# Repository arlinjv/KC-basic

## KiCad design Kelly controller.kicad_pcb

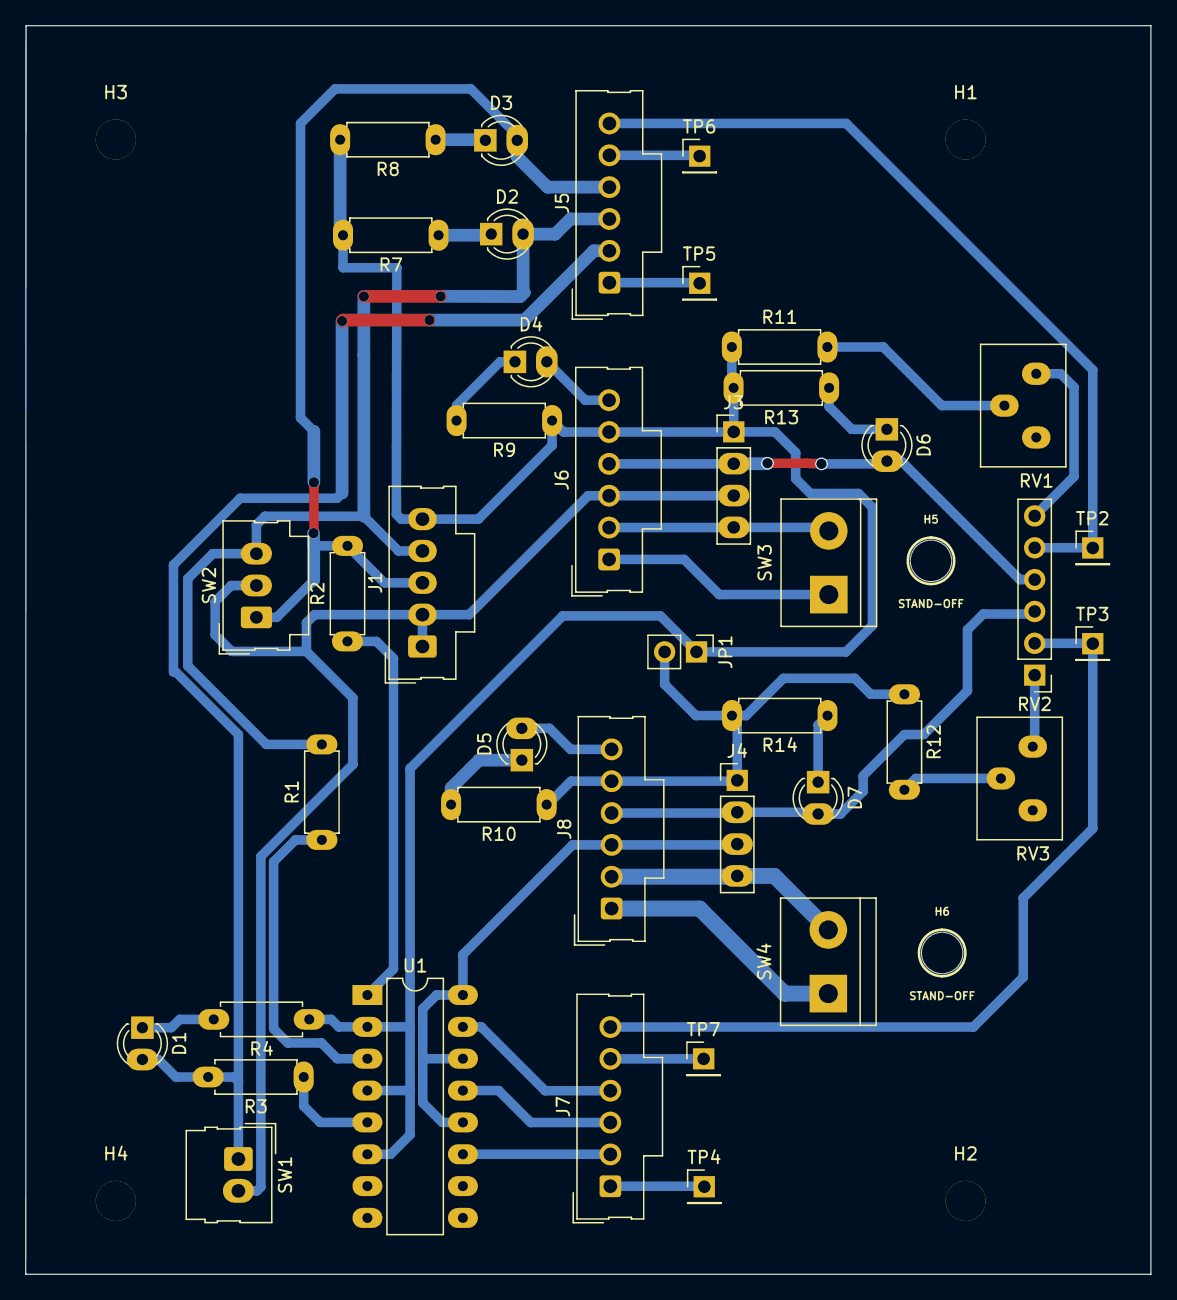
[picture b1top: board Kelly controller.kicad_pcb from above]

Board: 2 copper layers, 89.8 x 99.6 mm, 47 parts (0 on the bottom side), 38 nets.

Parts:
D1, D4, D5: yellow; LED_D3.0mm_wide_pads
D2, D3: green; LED_D3.0mm_wide_pads
D6, D7: RED; LED_D3.0mm_wide_pads
H1, H2, H3, H4: MountingHole; MountingHole_3.2mm_M3_through_hole
H5, H6: STAND-OFF
J1: FNR switch; Molex_SL_171971-0005_1x05_P2.54mm_Vertical
J3: A_5_12_48; PinHeader_1x04_P2.54mm_Vertical_wide_pads
J4: B_5_12_48; PinHeader_1x04_P2.54mm_Vertical_wide_pads
J5, J6, J7, J8: Conn_01x06_Female; Molex_SL_171971-0006_1x06_P2.54mm_Vertical
JP1: Jumper_2_Open; PinHeader_1x02_P2.54mm_Vertical
R1, R2, R3, R9, R10, R11, R12, R13, R14: 1k; R_Axial_DIN0207_L6.3mm_D2.5mm_P7.62mm_Horizontal_wide_pads
R4, R7, R8: 2.2k; R_Axial_DIN0207_L6.3mm_D2.5mm_P7.62mm_Horizontal_wide_pads
RV1, RV3: trim(1k); trimpot_breadboard_spacing
RV2: throttle(10k); PinHeader_1x06_P2.54mm_Vertical
SW1: Brake_SW; Molex_SL_171971-0002_1x02_P2.54mm_Vertical
SW2: FNR; Molex_SL_171971-0003_1x03_P2.54mm_Vertical_wide_pads
SW3, SW4: Power Switch; TerminalBlock_bornier-2_P5.08mm
TP2: T_A; PinHeader_1x01_P2.54mm_Vertical
TP3: T_B; PinHeader_1x01_P2.54mm_Vertical
TP4, TP5: ftsw; PinHeader_1x01_P2.54mm_Vertical
TP6, TP7: anbrk; PinHeader_1x01_P2.54mm_Vertical
U1: LTV-247; DIP-16_W7.62mm_LongPads

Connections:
+5VA: D6.2, J3.2, J6.4, RV2.4
+5VB: D7.2, J4.2, J8.4, RV2.3
+12VA: J1.1, J1.2, J3.3, J6.3, SW1.2, SW2.2
+12VB: J4.3, J8.3, U1.12, U1.14, U1.16
+48VA: J3.4, J6.2, SW3.2
+48VB: J4.4, J8.2, SW4.2
/Brake-A: D1.2, J5.2, R3.2, SW1.1
/Brake-B: J7.2, U1.11
/Brake_AN-A: J5.5, TP6.1
/Brake_AN-B: J7.5, TP7.1
/FWD-A: D3.2, J1.3, J5.4, R2.2, SW2.1
/FWD-B: J7.4, U1.15
/Foot_SW-A: J5.1, TP5.1
/Foot_SW-B: J7.1, TP4.1
/Meter-A: D4.2, J6.6
/Meter-B: D5.2, J8.6
/PWR-A: J6.1, SW3.1
/PWR-B: J8.1, SW4.1
/REV-A: D2.2, J1.4, J5.3, R1.2, SW2.3
/REV-B: J7.3, U1.13
/Throttle-A: J5.6, RV2.5, TP2.1
/Throttle-B: J7.6, RV2.2, TP3.1
GNDA: J1.5, J3.1, J6.5, JP1.1, R4.1, R7.2, R8.2, R9.1, R11.1, R13.2, U1.2, U1.4, U1.6
GNDB: J4.1, J8.5, JP1.2, R10.1, R12.1, R14.2
unnamed: D1.1, R4.2
unnamed: D2.1, R7.1
unnamed: D3.1, R8.1
unnamed: D4.1, R9.2
unnamed: D5.1, R10.2
unnamed: D6.1, R13.1
unnamed: D7.1, R14.1
unnamed: R1.1, U1.3
unnamed: R2.1, U1.1
unnamed: R3.1, U1.5
unnamed: R11.2, RV1.2
unnamed: R12.2, RV3.2
unnamed: RV1.1, RV2.6
unnamed: RV2.1, RV3.1

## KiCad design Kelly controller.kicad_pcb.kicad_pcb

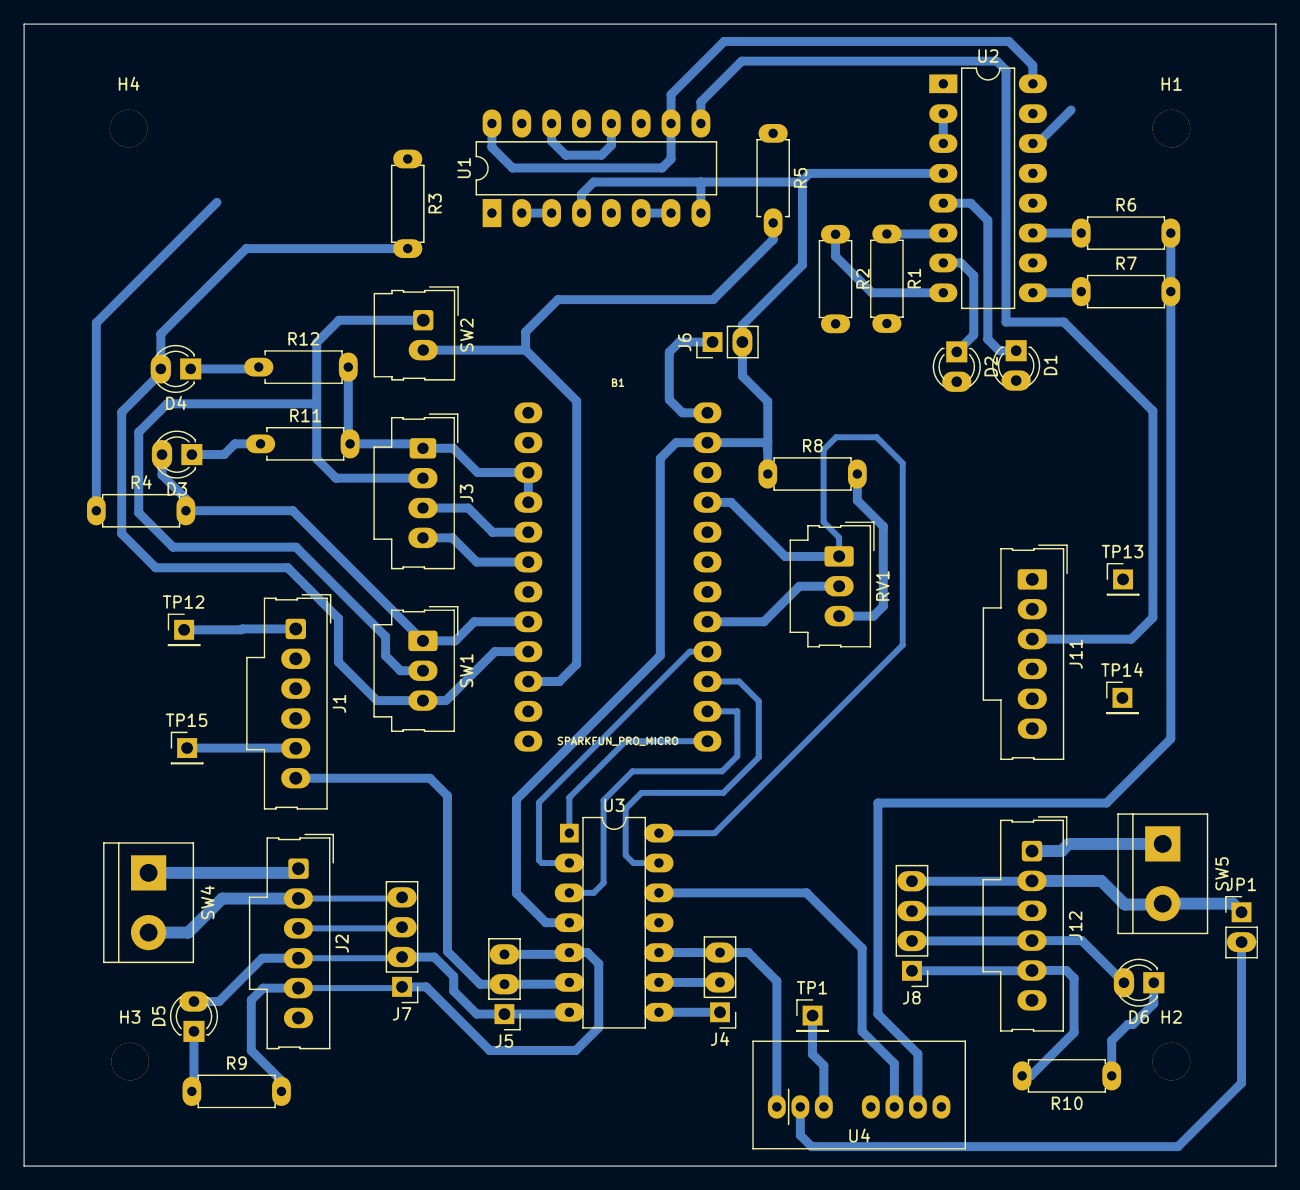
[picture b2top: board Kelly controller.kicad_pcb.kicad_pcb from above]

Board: 2 copper layers, 106.5 x 97.2 mm, 48 parts (0 on the bottom side), 56 nets.

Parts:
B1: SPARKFUN_PRO_MICRO
D1, D2: yellow; LED_D3.0mm_wide_pads
D3, D4: green; LED_D3.0mm_wide_pads
D5, D6: RED; LED_D3.0mm_wide_pads
H1, H2, H3, H4: MountingHole; MountingHole_3.2mm_M3_through_hole
J1, J2, J11, J12: Conn_01x06_Female; Molex_SL_171971-0006_1x06_P2.54mm_Vertical
J3: I2C throttle; Molex_SL_171971-0004_1x04_P2.54mm_Vertical_wide_pads
J4: throttle A; PinHeader_1x03_P2.54mm_Vertical_wide_pads
J5: throttle B; PinHeader_1x03_P2.54mm_Vertical_wide_pads
J6: Board power; PinHeader_1x02_P2.54mm_Vertical
J7: B_5_12_48; PinHeader_1x04_P2.54mm_Vertical_wide_pads
J8: A_5_12_48; PinHeader_1x04_P2.54mm_Vertical_wide_pads
JP1: Jumper; PinHeader_1x02_P2.54mm_Vertical
R1, R2, R8, R9, R10, R11, R12: 1k; R_Axial_DIN0207_L6.3mm_D2.5mm_P7.62mm_Horizontal_wide_pads
R3, R4, R5: 220; R_Axial_DIN0207_L6.3mm_D2.5mm_P7.62mm_Horizontal_wide_pads
R6, R7: 10k; R_Axial_DIN0207_L6.3mm_D2.5mm_P7.62mm_Horizontal_wide_pads
RV1: Throttle; Molex_SL_171971-0003_1x03_P2.54mm_Vertical_wide_pads
SW1: FNR; Molex_SL_171971-0003_1x03_P2.54mm_Vertical_wide_pads
SW2: Brake_SW; Molex_SL_171971-0002_1x02_P2.54mm_Vertical
SW4, SW5: Power Switch; TerminalBlock_bornier-2_P5.08mm
TP1: RC; PinHeader_1x01_P2.54mm_Vertical
TP12, TP13: ftsw; PinHeader_1x01_P2.54mm_Vertical
TP14, TP15: anbrk; PinHeader_1x01_P2.54mm_Vertical
U1, U2: LTV-247; DIP-16_W7.62mm_LongPads
U3: MCP4251; DIP-14_W7.62mm
U4: SPAN02C-05; SPAN02

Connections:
5V: B1.24, J6.1, U3.12, U4.6
+5VA: D6.2, J4.1, J8.2, J12.4, U3.8
+5VB: D5.2, J2.4, J5.1, J7.2, U3.7
+12VA: J8.3, J12.3, U1.10, U1.16, U2.16
+12VB: J2.3, J7.3, U1.12, U1.14, U2.14
+48VA: J8.4, J12.2, JP1.1, SW5.2
+48VB: J2.2, J7.4, SW4.2
/5-Reverse: B1.8, D3.2, R4.2, SW1.1
/6-Forward: B1.9, D4.2, R3.2, SW1.3
/7-Brake: B1.10, R5.2, SW2.2
/8-Meter_B: B1.11, R6.1, U2.11
/9-Meter_A: B1.12, R7.1, U2.9
/10-CS: B1.13, U3.1
/Brake-A: J11.2, U2.15
/Brake-B: J1.2, U2.13
/Brake_AN-A: J11.5, TP14.1
/Brake_AN-B: J1.5, TP15.1
/FWD-A: J11.4, U1.15
/FWD-B: J1.4, U1.13
/Foot_SW-A: J11.1, TP13.1
/Foot_SW-B: J1.1, TP12.1
/Meter-A: D2.2, J12.6
/Meter-B: D1.2, J2.6
/PWR-A: J12.1, SW5.1
/PWR-B: J2.1, SW4.1
/REV-A: J11.3, U1.9
/REV-B: J1.3, U1.11
/SCL: B1.6, J3.4
/SDA: B1.5, J3.3
/Throttle-A: J4.2, J11.6, U3.9
/Throttle-B: J1.6, J5.2, U3.6
GND: B1.3, B1.4, B1.23, J3.1, J6.2, R6.2, R7.2, R8.1, R11.2, R12.2, U1.4, U1.8, U2.4, U3.4, U4.7
GNDA: J4.3, J8.1, J12.5, R2.2, R10.2, U3.10, U4.1
GNDB: J2.5, J5.3, J7.1, R1.2, R9.2, U3.5
unnamed: B1.14, U3.3
unnamed: B1.15, U3.13
unnamed: B1.16, U3.2
unnamed: B1.17, RV1.2
unnamed: D1.1, U2.5
unnamed: D2.1, U2.7
unnamed: D3.1, R11.1
unnamed: D4.1, R12.1
unnamed: D5.1, R9.1
unnamed: D6.1, R10.1
unnamed: JP1.2, U4.2
unnamed: R1.1, U2.6
unnamed: R2.1, U2.8
unnamed: R3.1, U1.1
unnamed: R4.1, U1.5
unnamed: R5.1, U2.1
unnamed: R8.2, RV1.3
unnamed: TP1.1, U4.3
unnamed: U1.2, U1.3
unnamed: U1.6, U1.7
unnamed: U2.2, U2.3
VCC: B1.21, J3.2, RV1.1, SW1.2, SW2.1, U2.10, U2.12, U3.14

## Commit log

2021-11-02 first commit
    First version was used to finish out test platform
    Next goal with this board is to have control boards for first prototype
    mcu incorporation will come later
2021-11-02 removed auto connectors and added assembly connector
2021-11-02 Deleted old schematic from repository
2021-11-03 PCB routed and ready for cutting
2021-11-05 created gerber files
2021-11-05 updated vias
2021-11-05 trying to fix via sizes
2021-11-05 Split 12 pin connector realized did not have 12 pin connector so split roughly into power and controls cables redid pcb layout and exported gerbers;
2021-11-06 first board cut and connected successfully
    some minor changes to make before cutting second board, including removing battery connector and flipping some connectors
2021-11-07 Ready to cut second board
    Thickened 12V traces and removed batt connector which was superfluous
2022-01-07 minor routing changes to improve cutting time
2022-03-26 saving most recent changes in preparation for moving to mcu based schematics
2022-03-26 renamed repo at github. testing with change in git notes
2022-03-26 first commit on branch base. Incorporates minor change in schematic notes. Base branch will be useful for any fresh starts in the future.
2022-04-10 redid board. vias were too small and close together. Also changed many pads to oval
2022-04-21 Cut first attempt at twin motor arduino board. During assembly had several lifted pads - need to use wider traces where practical. Brake lines were wired wrong. See notes in this commit for history. 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
2022-05-21 Last version of mcp4251 based board. Too many problems but ultimately got to work by combining grounds and putting diodes in line with pot high side to get lower that Arduino Vcc. Next version will u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
2022-05-22 Getting ready to move on to new version without digital pots. Added some notes re. how got last board to work. Added jumpers to tie grounds together. Next version will be dead simple dual pot board. 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
2022-05-22 Dropping Arduino and digital pot. Using dual pot for control. This way can have total isolation between Kelly controllers. Currently have optoisolators in place for brake and FNR control. May switch 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
2022-05-22 removed arduino folder
2022-05-22 saved pdf of schematic for easy reference on github
2022-06-10 board ready to cut
